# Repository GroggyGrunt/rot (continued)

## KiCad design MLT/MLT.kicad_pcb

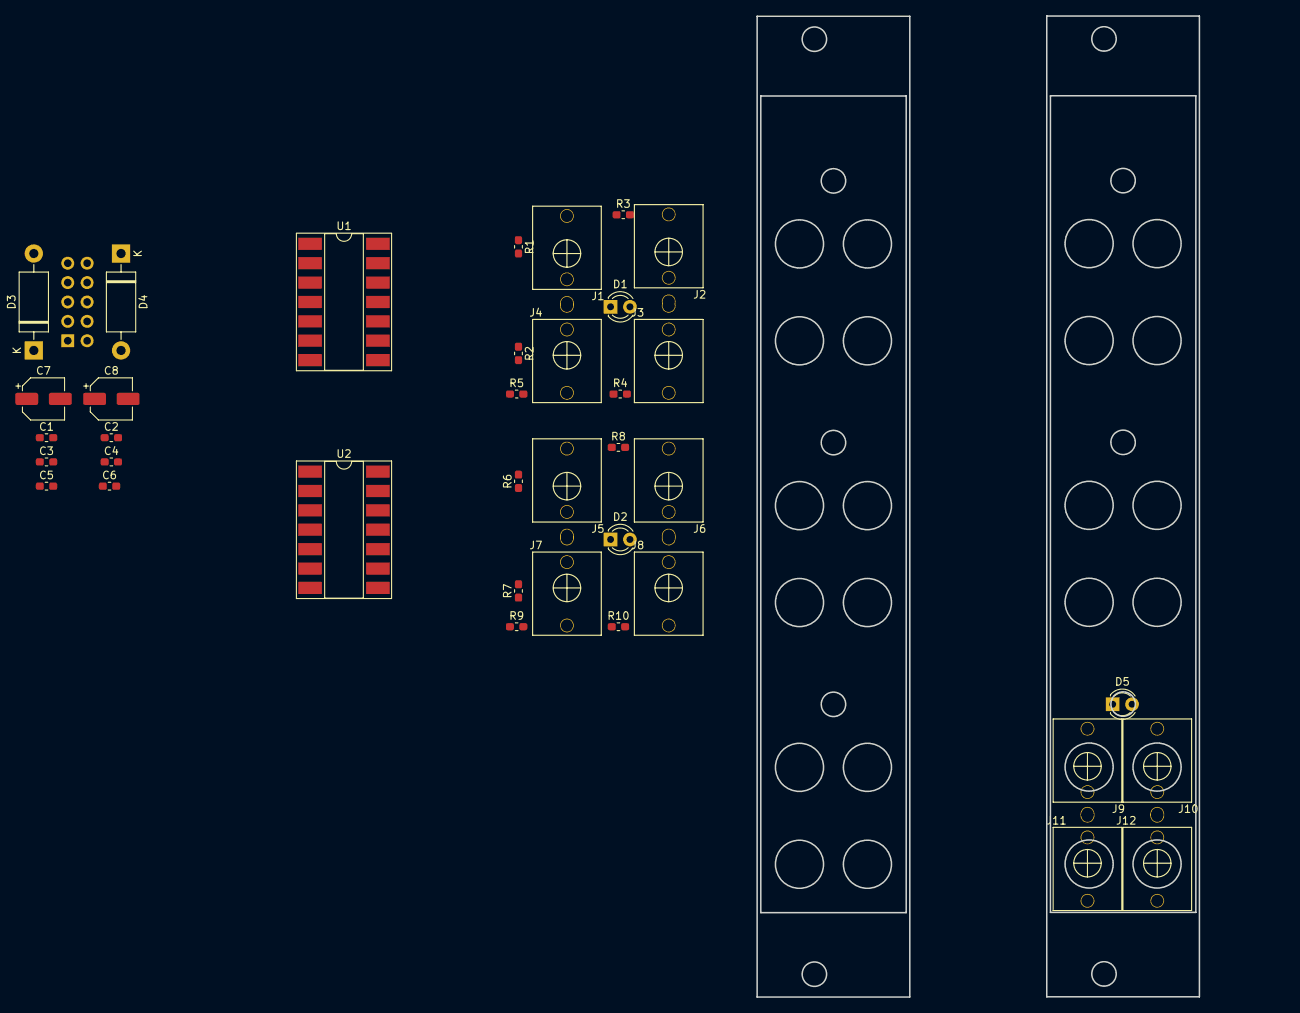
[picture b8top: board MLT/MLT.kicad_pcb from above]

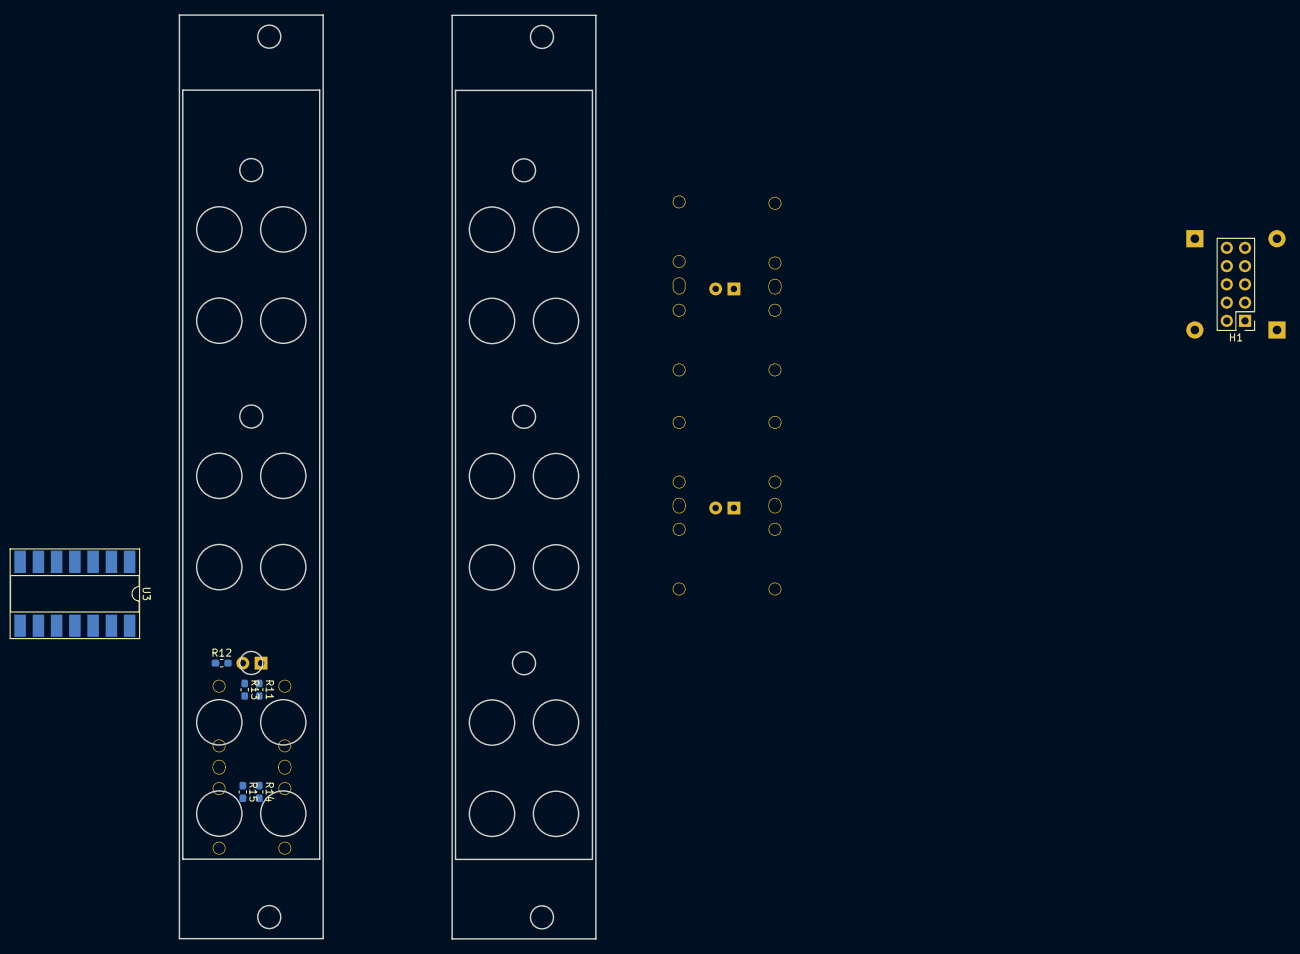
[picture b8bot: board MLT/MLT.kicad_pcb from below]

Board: 2 copper layers, 44 parts (7 on the bottom side), 32 nets, no tracks yet.

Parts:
C1, C2, C3, C4, C5, C6: 100n; C_0603_1608Metric_Pad1.05x0.95mm_HandSolder
C7, C8: 1.7u; CP_Elec_5x5.3
D1, D2, D5: LED; LED_D3.0mm_FlatTop
D3, D4: D; D_DO-15_P12.70mm_Horizontal
H1: PIN_HEADER_2x5; PinHeader_2x05_P2.54mm_Vertical
J1, J2, J3, J4, J5, J6, J7, J8, J9, J10, J11, J12: PJ301M-12
R1, R6, R11: 10m; R_0603_1608Metric_Pad1.05x0.95mm_HandSolder
R2, R7, R12: 1k; R_0603_1608Metric_Pad1.05x0.95mm_HandSolder
R3, R4, R5, R8, R9, R10, R13, R14, R15: 51; R_0603_1608Metric_Pad1.05x0.95mm_HandSolder
U1, U2, U3: TL074; DIP-14_W8.89mm_SMDSocket_LongPads

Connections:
GND: C1.2, C2.1, C3.2, C4.1, C5.2, C6.1, C7.2, C8.1, H1.3, H1.4, H1.5, H1.6, H1.7, H1.8, J1.1, J1.2, J2.1, J3.1, J4.1, J5.2, J5.3, J6.1, J7.1, J8.1, J9.1, J9.2, J10.1, J11.1, J12.1, R1.2, R2.1, R6.2, R7.1, R11.2, R12.1
unnamed: C1.1, C3.1, C5.1, C7.1, D3.1, U1.4, U2.4, U3.4
unnamed: C2.2, C4.2, C6.2, C8.2, D4.2, U1.11, U2.11, U3.11
unnamed: D1.1, U1.14
unnamed: D1.2, R2.2, U1.13
unnamed: D2.1, U2.14
unnamed: D2.2, R7.2, U2.13
unnamed: D3.2, H1.1, H1.2
unnamed: D4.1, H1.9, H1.10
unnamed: D5.1, U3.14
unnamed: D5.2, R12.2, U3.13
unnamed: J1.3, R1.1, U1.3, U1.5, U1.10, U1.12
unnamed: J2.3, R3.2
unnamed: J3.3, R4.2
unnamed: J4.3, R5.2
unnamed: J5.1, R6.1, U2.3, U2.5, U2.10, U2.12
unnamed: J6.3, R8.2
unnamed: J7.3, R9.2
unnamed: J8.3, R10.2
unnamed: J9.3, R11.1, U3.3, U3.5, U3.10, U3.12
unnamed: J10.3, R13.2
unnamed: J11.3, R14.2
unnamed: J12.3, R15.2
unnamed: R3.1, U1.1, U1.2
unnamed: R4.1, U1.6, U1.7
unnamed: R5.1, U1.8, U1.9
unnamed: R8.1, U2.1, U2.2
unnamed: R9.1, U2.6, U2.7
unnamed: R10.1, U2.8, U2.9
unnamed: R13.1, U3.1, U3.2
unnamed: R14.1, U3.6, U3.7
unnamed: R15.1, U3.8, U3.9

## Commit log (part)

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2019-01-11 Create simpleclock.ino
    added ino for atmega328p
2019-01-11 edit name
    edit name
2019-01-11 Create LICENSE
2019-01-11 edit max/minBpm
2019-01-11 Update GassTass-TicTok.ino
    raser edit
2019-01-11 added mcd
    added mcd
2019-01-11 reorg
2019-01-22 adding extra atmega for seven segment display with bpm over ic2
2019-03-18 at it again, adding transistors
2019-04-29 redesigning pcb
2019-04-29 added Tachometer
2019-05-01 all work
2019-05-01 added smd footprints
2019-05-02 ruffplaced pcb
2019-05-03 workworkwork
2019-05-03 tidy
2019-05-03 hmm
    hmm
2019-05-03 tidyu
2019-05-04 added some grafics
2019-05-04 edit readme
2019-05-04 replace and exp adding
2019-05-04 rebuildt and retraced
2019-05-04 added exp
2019-05-04 started exp
2019-05-04 exp pcb
2019-05-05 designing
2019-05-06 ntpv02 - single transistor
2019-05-06 locked panel
2019-05-06 added xray
2019-05-07 cleaned traces
2019-05-07 added mlt
2019-05-07 added
2019-05-07 Update fp-info-cache
2019-05-07 added panel
2019-05-07 rydding
2019-05-08 toutching up panel
2019-05-08 work work work
2019-05-08 panel
2019-05-08 panel finishing
2019-05-08 exp dirty scetch
2019-05-09 exp traced
2019-05-09 exp panel
2019-05-09 turn
2019-05-10 mlt update
2019-05-10 kasse
2019-05-10 added modulator
2019-05-11 added stuff..
2019-08-02 mixer enkel
